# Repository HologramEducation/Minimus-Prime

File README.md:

# Minimus-Prime

## Background

This is an experiment to shrink the logic and support circuitry around a cellular modem to the bare minimum and offer them as a surface mount solderable board. This design will be tested as a lightweight hardware device to connect to Hologram services.

### License

This design is OSHW

## Usage

This device is meant to work with uBlox cellular modems and the Hologram Global SIM card. To get a free SIM and 1 MB of data per month on the cellular plan, check out the [Developer Plan](https://hologram.io/devplan/)

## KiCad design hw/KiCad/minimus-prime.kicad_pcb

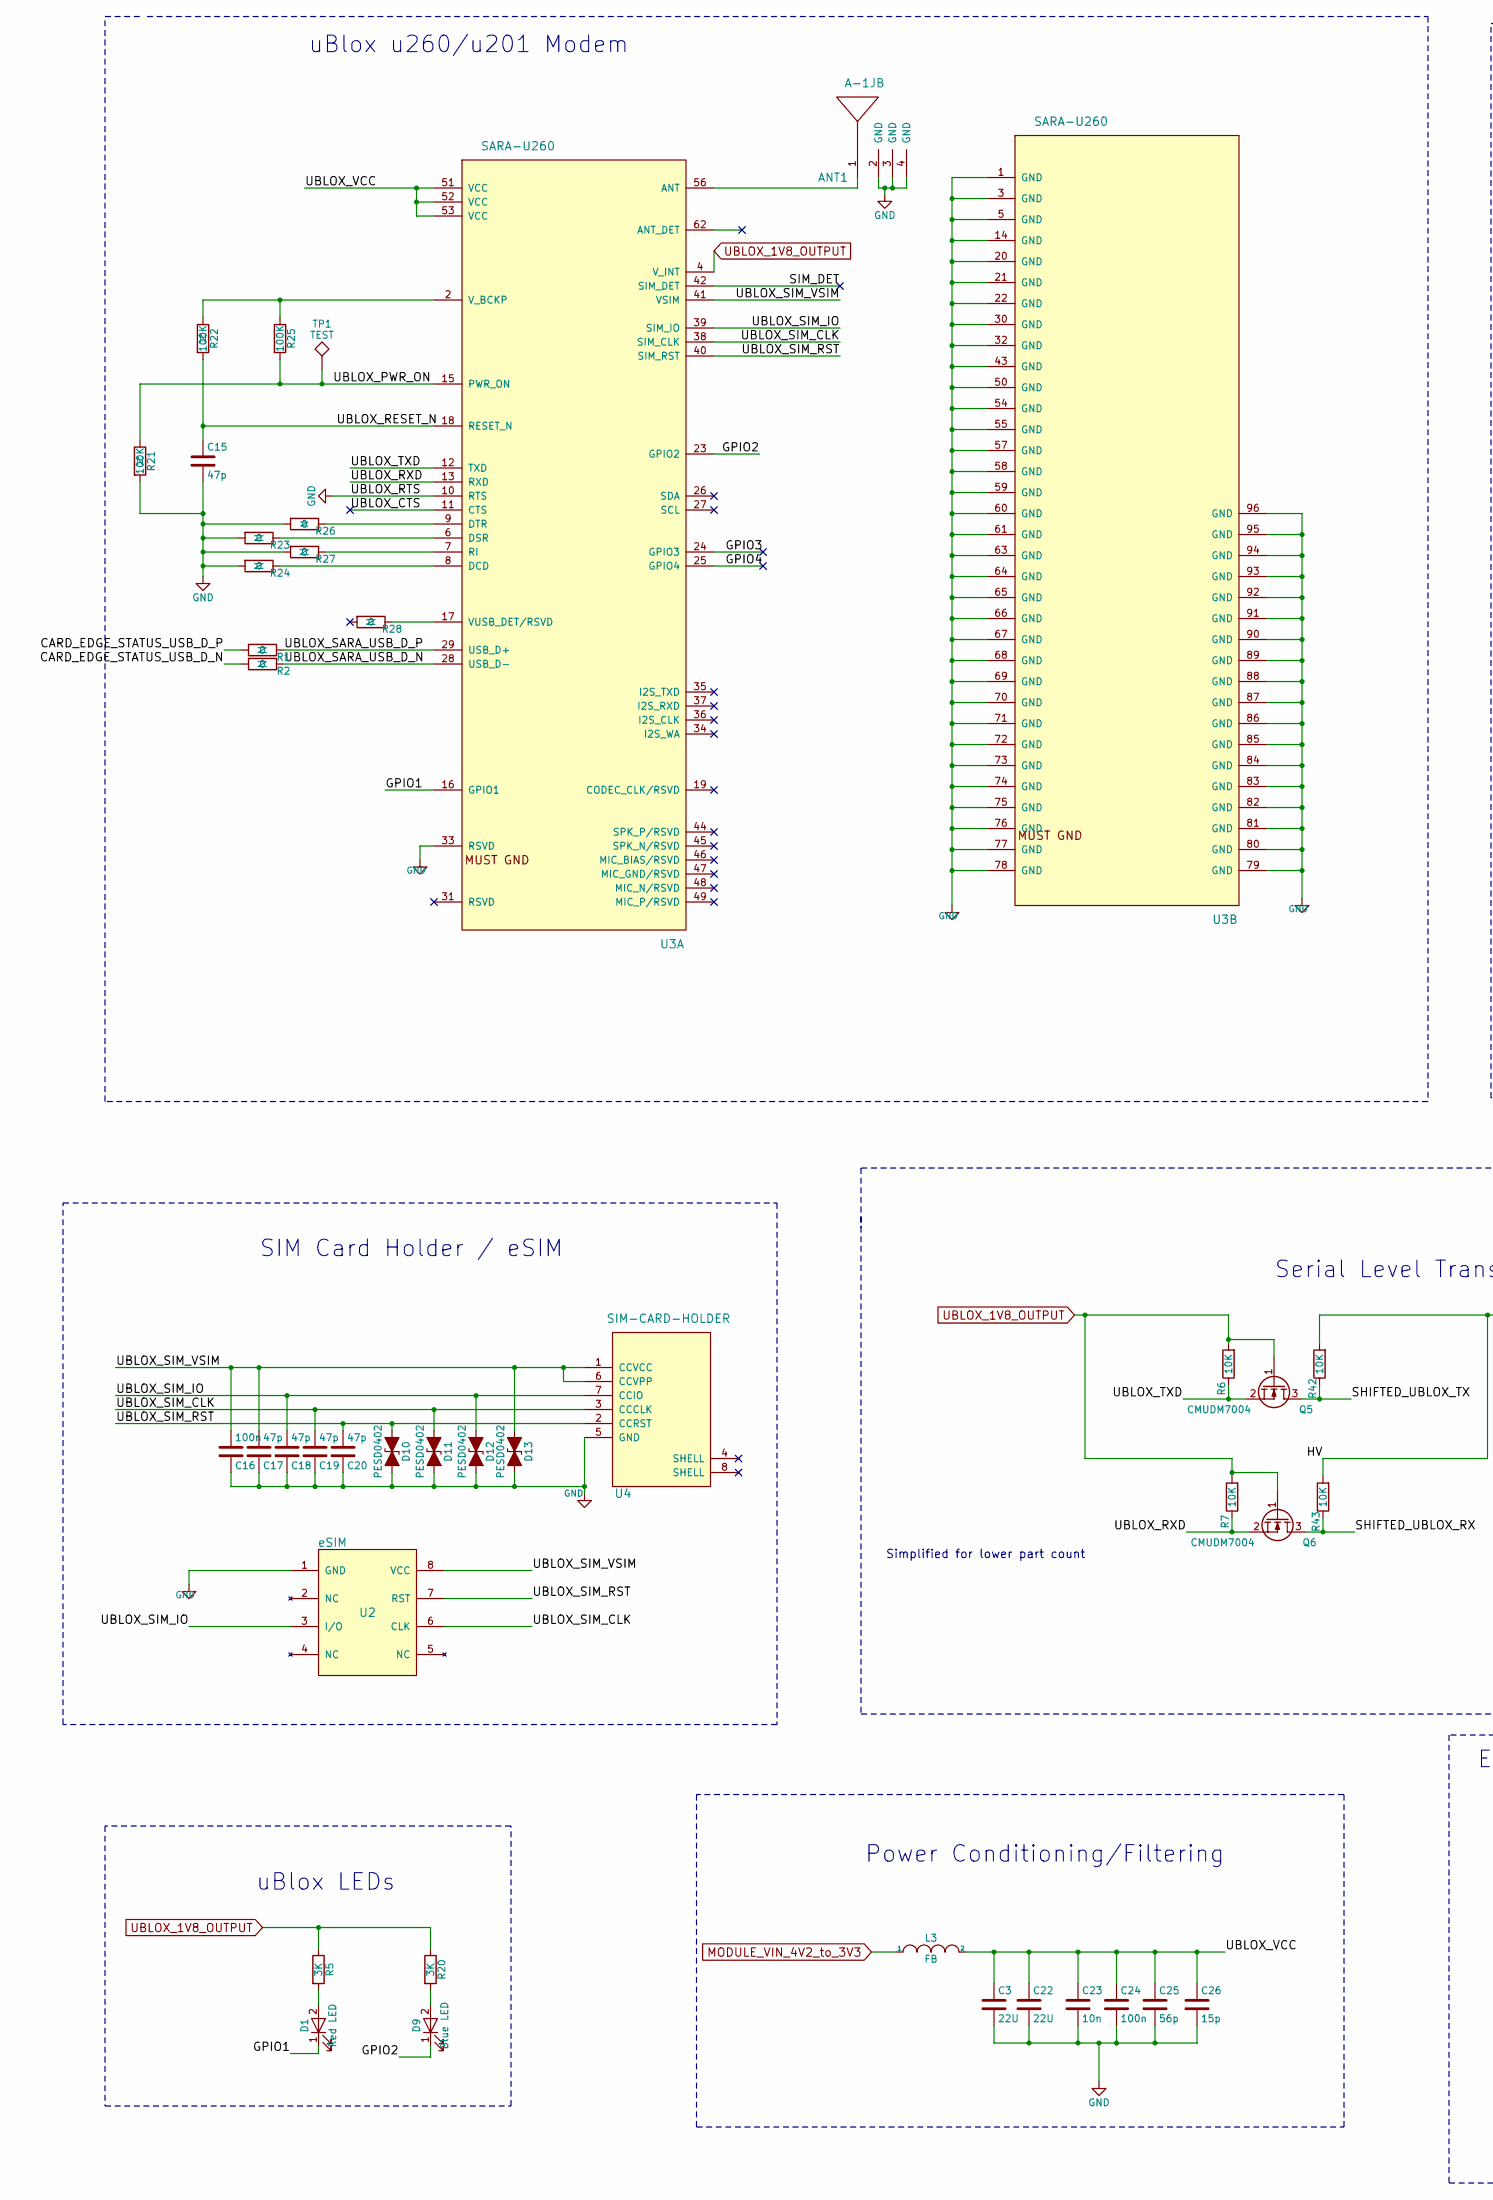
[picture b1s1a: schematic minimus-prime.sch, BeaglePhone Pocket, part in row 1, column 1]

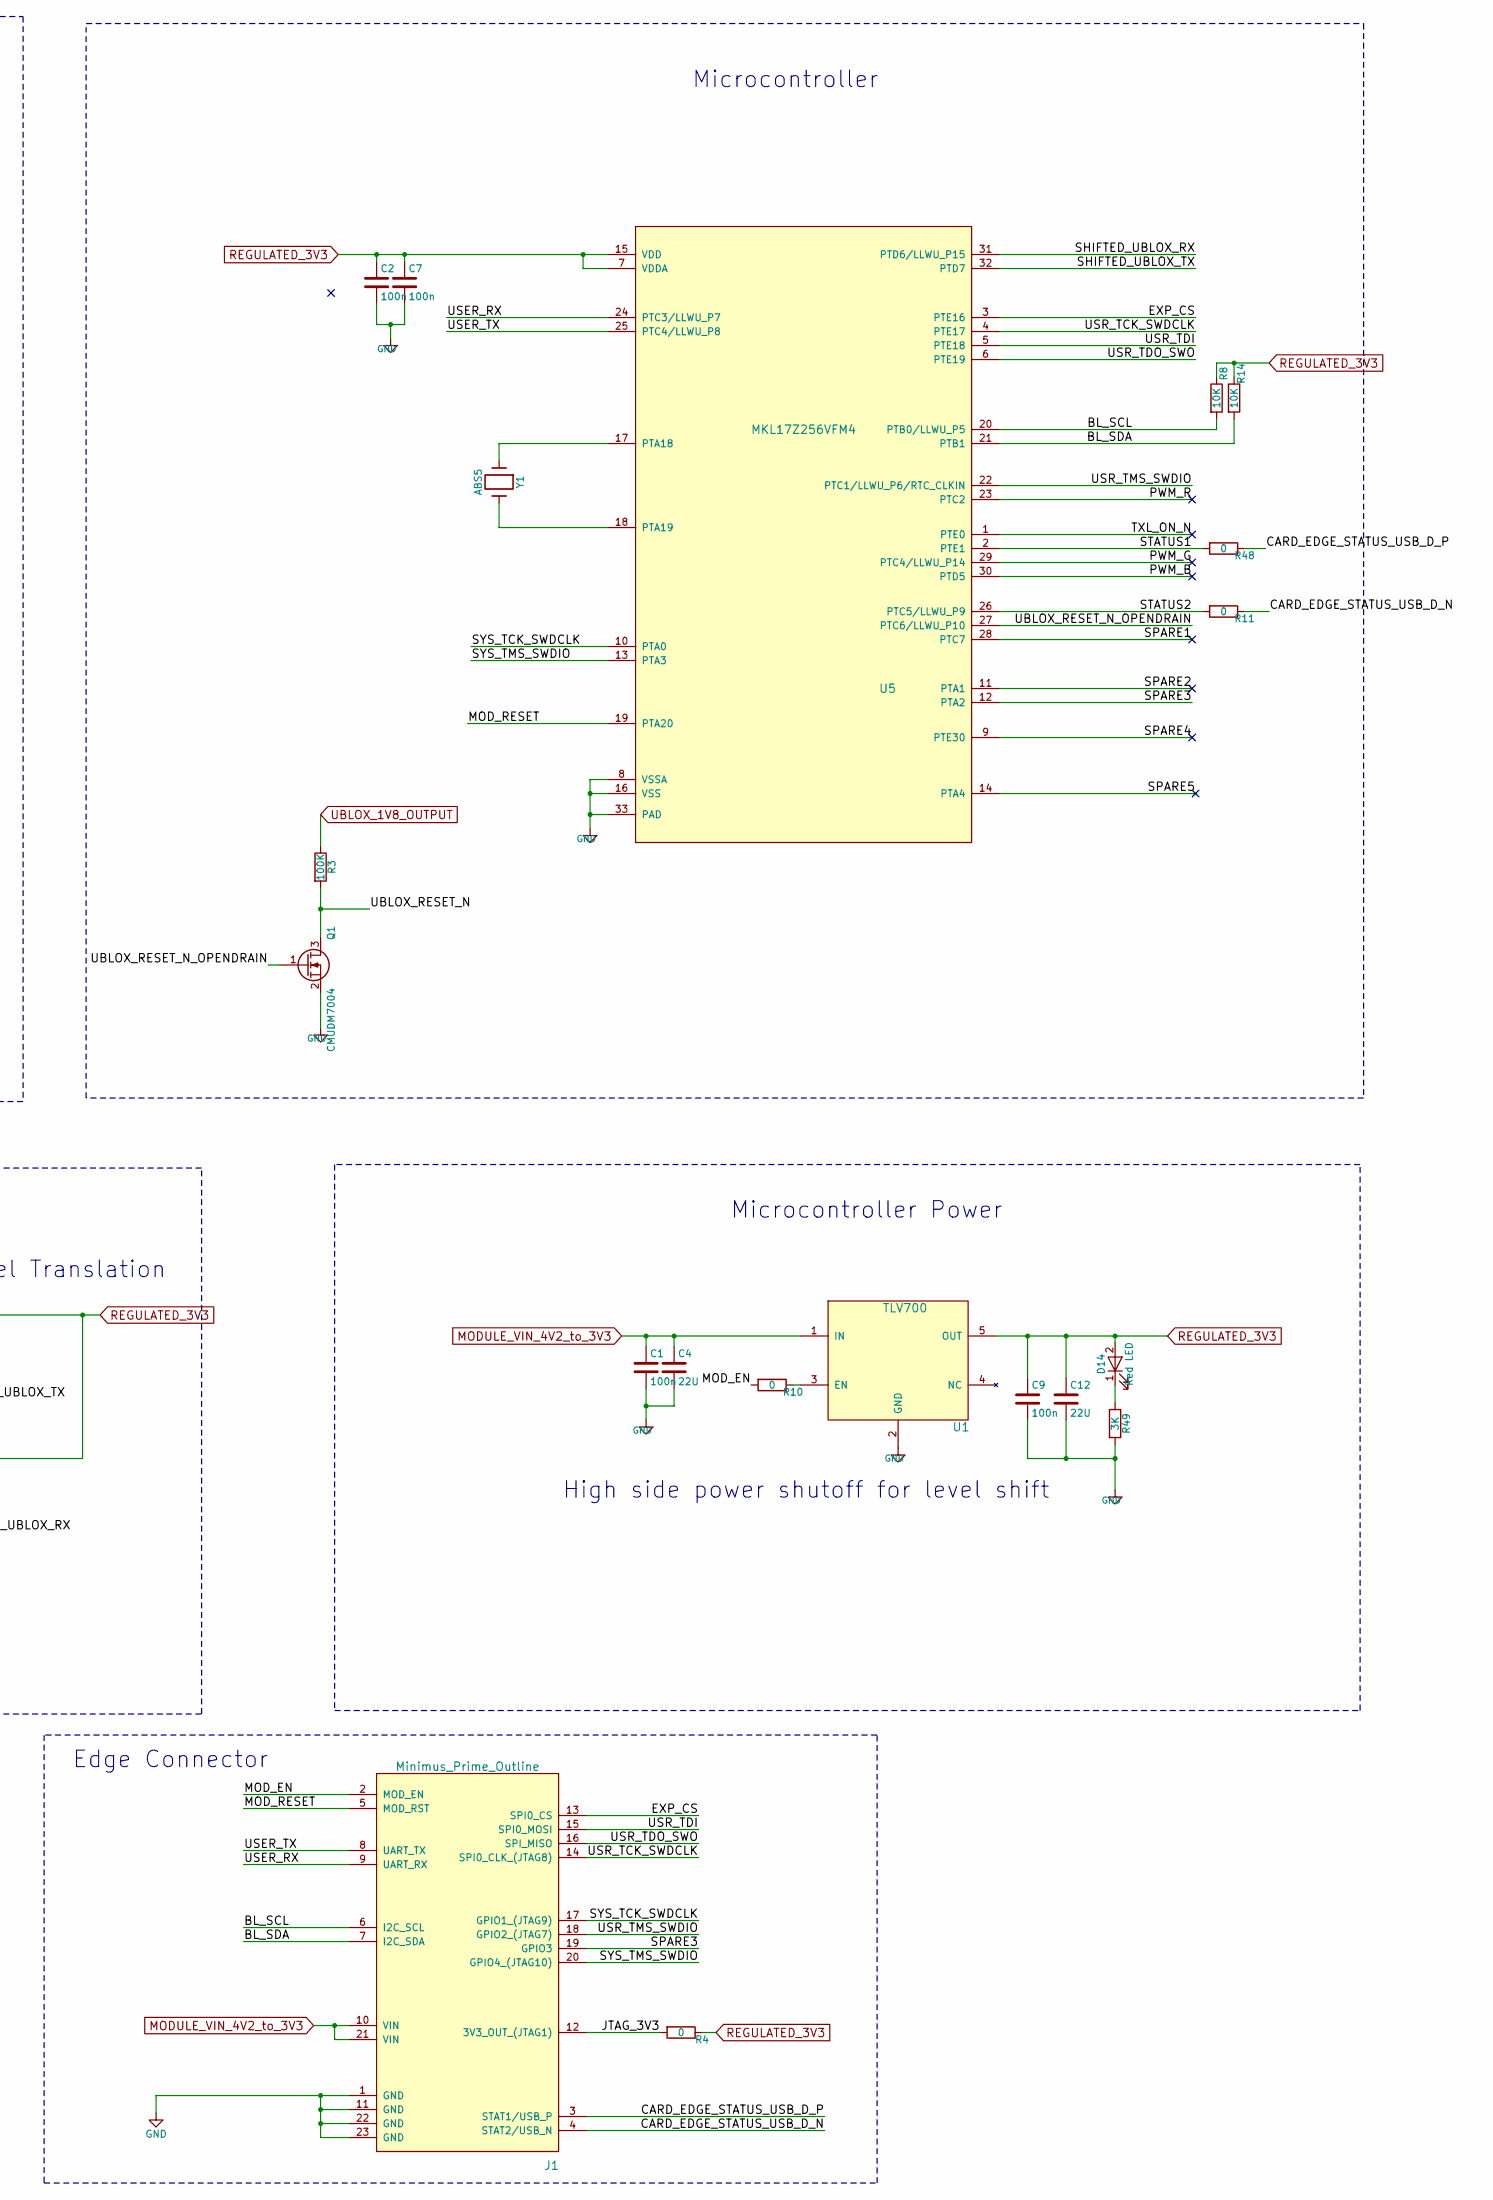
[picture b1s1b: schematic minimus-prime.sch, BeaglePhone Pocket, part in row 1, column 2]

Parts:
ANT1: A-1JB; MPN A-1JB
C1, C2, C7, C9, C16, C24: 100n; C_0402; MPN GRM155R71C104KA88J
C3, C22: 22U; C_0805; MPN CL21A226MOCLRNC
C4, C12: 22U; C_0603; MPN GRM188R60J226MEA0D
C15, C17, C18, C19, C20: 47p; C_0402; MPN GRM1555C1H470JA01
C23: 10n; C_0402; MPN GRM1555C1H100JA01D
C25: 56p; C_0402; MPN GRM1555C1H560JA01D
C26: 15p; C_0402; MPN GJM1555C1H150JB01D
D1, D14: Red LED; LED_0402; MPN VLMS1500-GS08
D9: Blue LED; LED_0402; MPN VLMB1500-GS08
D10, D11, D12, D13: PESD0402; R_0402; MPN PESD0402-140
J1: Minimus_Prime_Outline
L3: FB; R_0603; MPN BLM18AG121SN1D
Q1, Q5, Q6: CMUDM7004; SOT-523; MPN CMUDM7004
R1, R2, R4, R10, R11, R23, R24, R26, R27, R28, R48: 0; R_0402; MPN RC0402JR-070RL
R3, R21, R22, R25: 100K; R_0402; MPN RC0402FR-07100KL
R5, R20, R49: 3K; R_0402; MPN RC0402JR-073KL
R6, R7, R8, R14, R42, R43: 10K; R_0402; MPN RC0402JR-0710KL
TP1: TEST
U1: TLV700; SOT-23-5; MPN TLV70033DDCR
U2: eSIM; DFN-8-1EP_6x5mm_Pitch1.27mm_SmallFlag; MPN eSIM
U3: SARA-U260; SARA-G3-U2; MPN SARA-U260-00S
U4: SIM-CARD-HOLDER; SIM8050-6-0-14-01-A; MPN SIM8050-6-0-14-01-A
U5: MKL17Z256VFM4; QFN-32-1EP_5x5mm_Pitch0.5mm; MPN MKL17Z256VFM4
Y1: ABS5; ABS05; MPN ABS05-32.768KHZ-T

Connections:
/BL_SCL: J1.6 (I2C_SCL), R8.2, U5.20 (PTB0/LLWU_P5)
/BL_SDA: J1.7 (I2C_SDA), R14.2, U5.21 (PTB1)
/CARD_EDGE_STATUS_USB_D_N: J1.4 (STAT2/USB_N), R2.2, R11.1
/CARD_EDGE_STATUS_USB_D_P: J1.3 (STAT1/USB_P), R1.2, R48.1
/EXP_CS: J1.13 (SPI0_CS), U5.3 (PTE16)
/GPIO1: D1.1 (K), U3.16 (GPIO1)
/GPIO2: D9.1 (K), U3.23 (GPIO2)
/GPIO3: U3.24 (GPIO3)
/GPIO4: U3.25 (GPIO4)
/MOD_EN: J1.2 (MOD_EN), R10.2
/MOD_RESET: J1.5 (MOD_RST), U5.19 (PTA20)
/PWM_B: U5.30 (PTD5)
/PWM_G: U5.29 (PTC4/LLWU_P14)
/PWM_R: U5.23 (PTC2)
/SHIFTED_UBLOX_RX: Q6.3 (D), R43.1, U5.31 (PTD6/LLWU_P15)
/SHIFTED_UBLOX_TX: Q5.3 (D), R42.1, U5.32 (PTD7)
/SIM_DET: U3.42 (SIM_DET)
/SPARE1: U5.28 (PTC7)
/SPARE2: U5.11 (PTA1)
/SPARE3: J1.19 (GPIO3), U5.12 (PTA2)
/SPARE4: U5.9 (PTE30)
/SPARE5: U5.14 (PTA4)
/STATUS1: R48.2, U5.2 (PTE1)
/STATUS2: R11.2, U5.26 (PTC5/LLWU_P9)
/SYS_TCK_SWDCLK: J1.17 (GPIO1_(JTAG9)), U5.10 (PTA0)
/SYS_TMS_SWDIO: J1.20 (GPIO4_(JTAG10)), U5.13 (PTA3)
/TXL_ON_N: U5.1 (PTE0)
/UBLOX_CTS: U3.11 (CTS)
/UBLOX_PWR_ON: R21.1, R25.2, TP1.1, U3.15 (PWR_ON)
/UBLOX_RESET_N: C15.1, Q1.3 (D), R3.2, R22.2, U3.18 (RESET_N)
/UBLOX_RESET_N_OPENDRAIN: Q1.1 (G), U5.27 (PTC6/LLWU_P10)
/UBLOX_RXD: Q6.2 (S), R7.1, U3.13 (RXD)
/UBLOX_SARA_USB_D_N: R2.1, U3.28 (USB_D-)
/UBLOX_SARA_USB_D_P: R1.1, U3.29 (USB_D+)
/UBLOX_SIM_CLK: C19.2, D11.1 (A1), U2.6 (CLK), U3.38 (SIM_CLK), U4.3 (CCCLK)
/UBLOX_SIM_IO: C18.2, D12.1 (A1), U2.3 (I/O), U3.39 (SIM_IO), U4.7 (CCIO)
/UBLOX_SIM_RST: C20.2, D10.1 (A1), U2.7 (RST), U3.40 (SIM_RST), U4.2 (CCRST)
/UBLOX_SIM_VSIM: C16.2, C17.2, D13.1 (A1), U2.8 (VCC), U3.41 (VSIM), U4.1 (CCVCC), U4.6 (CCVPP)
/UBLOX_TXD: Q5.2 (S), R6.1, U3.12 (TXD)
/UBLOX_VCC: C3.1, C22.1, C23.1, C24.1, C25.1, C26.1, L3.2, U3.51 (VCC), U3.52 (VCC), U3.53 (VCC)
/USER_RX: J1.9 (UART_RX), U5.24 (PTC3/LLWU_P7)
/USER_TX: J1.8 (UART_TX), U5.25 (PTC4/LLWU_P8)
/USR_TCK_SWDCLK: J1.14 (SPI0_CLK_(JTAG8)), U5.4 (PTE17)
/USR_TDI: J1.15 (SPI0_MOSI), U5.5 (PTE18)
/USR_TDO_SWO: J1.16 (SPI_MISO), U5.6 (PTE19)
/USR_TMS_SWDIO: J1.18 (GPIO2_(JTAG7)), U5.22 (PTC1/LLWU_P6/RTC_CLKIN)
GND: ANT1.2 (GND), ANT1.3 (GND), ANT1.4 (GND), C1.2, C2.2, C3.2, C4.2, C7.2, C9.2, C12.2, C15.2, C16.1, C17.1, C18.1, C19.1, C20.1, C22.2, C23.2, C24.2, C25.2, C26.2, D10.2 (A2), D11.2 (A2), D12.2 (A2), D13.2 (A2), J1.1 (GND), J1.11 (GND), J1.22 (GND), J1.23 (GND), Q1.2 (S), R21.2, R23.2, R24.2, R26.2, R27.2, R49.2, U1.2 (GND), U2.1 (GND), U3.1 (GND), U3.3 (GND), U3.5 (GND), U3.10 (RTS), U3.14 (GND), U3.20 (GND), U3.21 (GND), U3.22 (GND), U3.30 (GND), U3.32 (GND), U3.33 (RSVD), U3.43 (GND), U3.50 (GND), U3.54 (GND), U3.55 (GND), U3.57 (GND), U3.58 (GND), U3.59 (GND), U3.60 (GND), U3.61 (GND), U3.63 (GND), U3.64 (GND), U3.65 (GND), U3.66 (GND), U3.67 (GND), U3.68 (GND), U3.69 (GND), U3.70 (GND), U3.71 (GND), U3.72 (GND), U3.73 (GND), U3.74 (GND), U3.75 (GND), U3.76 (GND), U3.77 (GND), U3.78 (GND), U3.79 (GND), U3.80 (GND), U3.81 (GND), U3.82 (GND), U3.83 (GND), U3.84 (GND), U3.85 (GND), U3.86 (GND), U3.87 (GND), U3.88 (GND), U3.89 (GND), U3.90 (GND), U3.91 (GND), U3.92 (GND), U3.93 (GND), U3.94 (GND), U3.95 (GND), U3.96 (GND), U4.5 (GND), U5.8 (VSSA), U5.16 (VSS), U5.33 (PAD)
MODULE_VIN_4V2_to_3V3: C1.1, C4.1, J1.10 (VIN), J1.21 (VIN), L3.1, U1.1 (IN)
unnamed: ANT1.1, U3.56 (ANT)
unnamed: D1.2 (A), R5.2
unnamed: D9.2 (A), R20.2
unnamed: D14.1 (K), R49.1
unnamed: R10.1, U1.3 (EN)
unnamed: R22.1, R25.1, U3.2 (V_BCKP)
unnamed: R23.1, U3.6 (DSR)
unnamed: R24.1, U3.8 (DCD)
unnamed: R26.1, U3.9 (DTR)
unnamed: R27.1, U3.7 (RI)
unnamed: R28.1, U3.17 (VUSB_DET/RSVD)
unnamed: U5.17 (PTA18), Y1.1
unnamed: U5.18 (PTA19), Y1.2
UBLOX_1V8_OUTPUT: Q5.1 (G), Q6.1 (G), R3.1, R5.1, R6.2, R7.2, R20.1, U3.4 (V_INT)

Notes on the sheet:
Serial Level Translation
uBlox LEDs
uBlox u260/u201 Modem
SIM Card Holder / eSIM
Power Conditioning/Filtering
High side power shutoff for level shift
Simplified for lower part count
Edge Connector
Microcontroller Power
Microcontroller

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
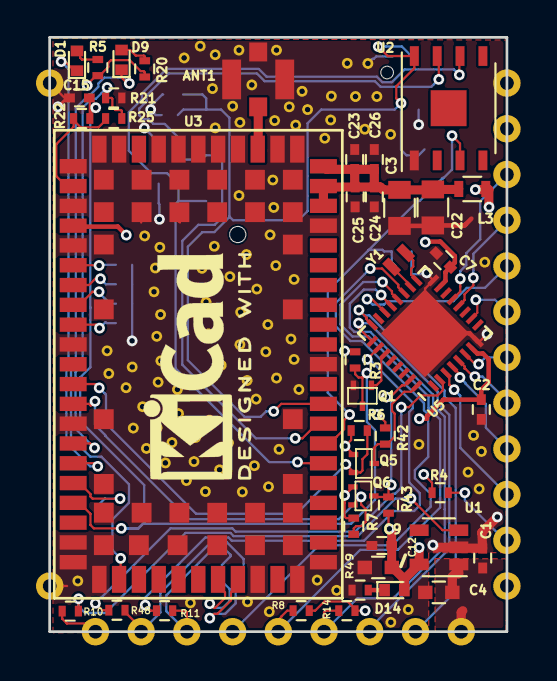
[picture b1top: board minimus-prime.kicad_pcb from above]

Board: 4 copper layers, 25.4 x 33.0 mm, 61 parts (0 on the bottom side), 52 nets.

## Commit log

2018-01-20 Pulled in old file (renamed) from the beaglephone-pocket project
2018-01-20 Removed dead libraries
2018-01-20 Added m0 and linear reg to schematic
2018-01-20 Started adding signal names
2018-01-20 Annotated schematic for new components
2018-01-20 Assigned footprints (not final) to get initial fitting
2018-01-20 Added another LED and generated initial netlist
2018-01-20 Added a left and right 01x14 connector and a 01x08 connector to simulate edge connections
2018-01-20 Decided to move board out by an additional .1 inch, total dimensions now roughly 1.1x1.4
2018-01-20 Preliminary pinout for card edge
2018-01-20 Started creating power zones
2018-01-21 Got rid of 330 uF cap
2018-01-21 Switching to SOT523 part for level shifter
2018-01-21 Removed a bunch of level shifter parts
2018-01-21 Started routing final data lines
2018-01-21 Removed USB components and connections
2018-01-21 First pass placement done, layout in final stages, off for schematic review
2018-01-21 Almost finished routing early board, updating from Ben L's suggestions
2018-01-21 Implemented some of the changes, lengthend the card edge
2018-01-21 Created another plane for module Vin
2018-01-21 Changed net names for clarity
2018-01-21 Added open drain FET for reset line
2018-01-21 Finished routing power to micro
2018-01-21 Added 3V3 to card edge for JTAG
2018-01-21 Added markers for external pins
2018-01-21 Added silkscreen logo, started DRC
2018-01-21 Removed all orginal DRC errors
2018-01-21 Changed name of external reset (mod_reset) and hooked into the previous pushbutton pin
2018-01-21 Swapped some pins to preserve PWM pins for adding a tricolor LED in the future
2018-01-21 Added all silkscreen logos
2018-01-21 Hid all the info layers
2018-01-22 Added Gerbers, converted old BOM
2018-01-22 Add picture to readme
2018-01-22 Broken trace found by fab house, good lord
2018-01-22 Generated gerbers for v1.1
2018-01-22 Added outline drawings
2018-01-22 Print to US letter sized paper for scaling
2018-01-22 Added one more US letter outline drawing
2018-01-23 Added eagle footprint
2018-01-25 exported csv using kifield
2018-01-25 Updated population for parts on the board using kifield
2018-01-25 Resetting
2018-02-05 Added a new symbol to represent the module edge
2018-02-05 Changed revision number and updated edge connector
2018-02-05 Moved Eagle and KiCad to a hw folder for top level consistency
2018-02-06 Added a new footpring for the host part of the module
2018-02-07 Removed old backup files at top level
2018-02-07 removed old csv files and generated a new one
2018-02-07 updated BOM with combined parts and placement data
2018-02-12 Created gitignore and modified README
2018-02-12 Revised gitignore
2018-02-13 generated pos data
2018-02-13 Changed notes on schematic page
2018-02-13 Generated package including placement data and schematic
2018-02-16 Remove non Hologram docs
2018-03-06 Added fab drawings to the DWG layer and generated docs for fabrication
